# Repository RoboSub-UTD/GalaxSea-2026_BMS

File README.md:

# GalaxSea 2026 Battery Management System

The battery management system for GalaxSea 2026 Roboboat

## Documentation
[Add link to documentation folder here]

## Getting started 
Clone the project with `git clone https://github.com/RoboSub-UTD/GalaxSea-2026_BMS.git` 

## Prerequsities 
Ensure the following tools are installed: 
- make 
- cmake
- gcc-arm-none-eabi
- openocd 
- gdb-multiarch
- CubeMX (Standalone or included with STM32CubeIDE)

> [!NOTE] 
> Installation of some of these tools on a Windows environment may require use of toolchains such as MYSY2 or Cygwin. Installing Windows Subsystem for Linux (WSL2) or using a Linux virtual machine are both viable alternatives.

### Installing USB Passthrough (WSL2)
Read this section if you are setting up your build environment through WSL2. You may skip this section otherwise.

USB passthrough is required for WSL2 because WSL2 is essentially a lightweight VM that does not have access to external USB devices by default. We can allow WSL to access USB devices through the use of usbipd-win which can be installed via the following link. The link also includes instructions on how to bind usb devices to WSL2.

usbipd-win Installation Link: https://github.com/dorssel/usbipd-win

> [!TIP]
> Binding devices using usbipd-win requires using the command line. If you prefer to use a GUI then it's reccomended to install 
> `wsl-usb-manager` here 
> https://github.com/nickbeth/wsl-usb-manager

## Recommended VS Code extensions
```
twxs.cmake
marus25.cortex-debug
ms-vscode.vscode-serial-monitor
ms-vscode.makefile-tools
ms-vscode.cmake-tools
ms-vscode.cpptools
ms-vscode.cpptools-extension-pack
ms-vscode.cpptools-themes
mcu-debug.rtos-views
mcu-debug.debug-tracker-vscode
mcu-debug.memory-view
mcu-debug.peripheral-viewer
```

## How to run Firmware

`cwd = bms`  

1. mkdir build && cd build 
2. cmake .. 
3. cmake --build build
## How to Contribute: 

Development of new features will be done on a separate branch other than main and will be merged with a pull request

## ARM Cortex Debug Configuration 
ARM Cortex Debug is a handy VS Code extension that integrates a IDE-like debugger for ARM microcontrollers into VS Code. To set up the debugger follow the instructions below.

1. Type the following command in the top bar: `>Debug: Add Configuration` to generate a 
`launch.json` file in the `.vscode` directory (usually hidden by default). 

2. Navigate and open up the `.vscode/launch.json` file.

3. Copy and paste the following JSON formatted code into the `launch.json` file. This will enable the use of openocd and gdb-mulitarch
by the Cortex Debug extension.

```
{
    "version": "0.2.0",
    "configurations": [
        {
            "name": "Debug (OpenOCD)",
            "cwd": "${workspaceFolder}",
            "executable": "${workspaceFolder}/bms/build/bms.elf",
            "request": "launch",
            "type": "cortex-debug",
            "servertype": "openocd",
            "interface": "swd",
            "device": "STM32H7532ZI",
            "runToEntryPoint": "main",
            "showDevDebugOutput": "raw",
            "configFiles": [
                "/usr/share/openocd/scripts/interface/stlink.cfg",
                "/usr/share/openocd/scripts/target/stm32h7x.cfg"
            ],
            "preLaunchCommands": [
                "set mem inaccessible-by-default off",
                "monitor reset"
            ],
            "postLaunchCommands": [
                "monitor reset init",
                "monitor sleep 200"
            ],
            "armToolchainPath": "/usr/bin/",
            "gdbPath": "/usr/bin/gdb-multiarch"
        }
    ]
}
```

4. Next, build and compile the binary executable for the project if you haven't already. 

5. Now, press the `Run` option on the top toolbar and select the first option `Start Debugging`
to start a session of Cortex debug. Cortex debug should flash the program to the MCU and highlight the starting point of the program in yellow. On the top right, a toolbar should appear with a few commands for debugging the program.

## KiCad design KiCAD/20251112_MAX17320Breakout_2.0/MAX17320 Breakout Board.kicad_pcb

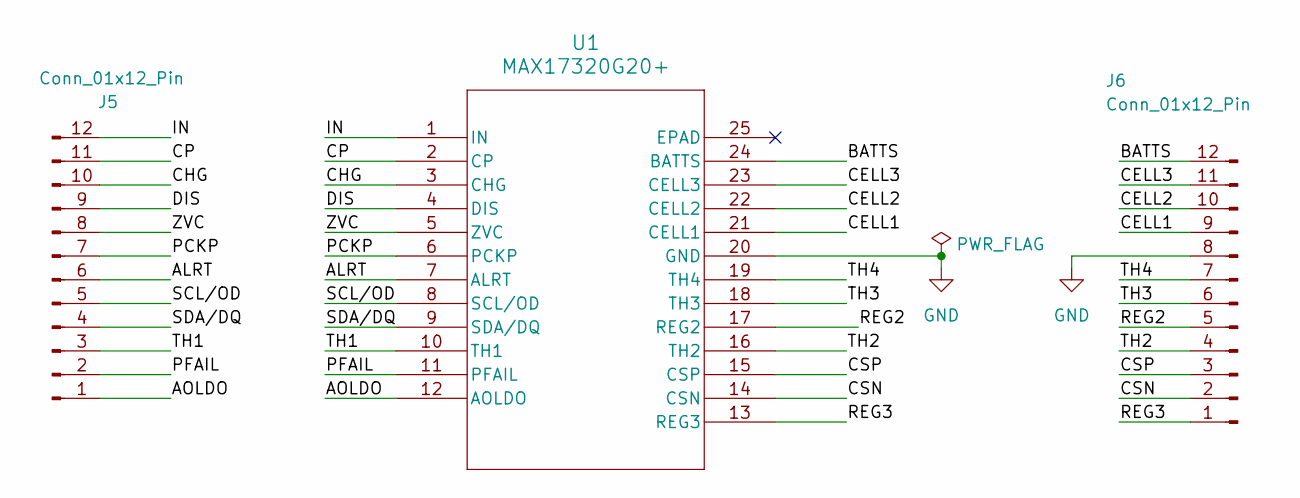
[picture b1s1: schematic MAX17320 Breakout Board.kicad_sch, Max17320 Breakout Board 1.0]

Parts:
J5, J6: Conn_01x12_Pin; PinHeader_1x12_P2.54mm_Vertical
U1: MAX17320G20+; 21-0139I_T2444-4_MXM

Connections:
/ALRT: J5.6, U1.7 (ALRT)
/AOLDO: J5.1, U1.12 (AOLDO)
/BATTS: J6.12, U1.24 (BATTS)
/CELL1: J6.9, U1.21 (CELL1)
/CELL2: J6.10, U1.22 (CELL2)
/CELL3: J6.11, U1.23 (CELL3)
/CHG: J5.10, U1.3 (CHG)
/CP: J5.11, U1.2 (CP)
/CSN: J6.2, U1.14 (CSN)
/CSP: J6.3, U1.15 (CSP)
/DIS: J5.9, U1.4 (DIS)
/IN: J5.12, U1.1 (IN)
/PCKP: J5.7, U1.6 (PCKP)
/PFAIL: J5.2, U1.11 (PFAIL)
/REG2: J6.5, U1.17 (REG2)
/REG3: J6.1, U1.13 (REG3)
/SCL/OD: J5.5, U1.8 (SCL/OD)
/SDA/DQ: J5.4, U1.9 (SDA/DQ)
/TH1: J5.3, U1.10 (TH1)
/TH2: J6.4, U1.16 (TH2)
/TH3: J6.6, U1.18 (TH3)
/TH4: J6.7, U1.19 (TH4)
/ZVC: J5.8, U1.5 (ZVC)
GND: J6.8, U1.20 (GND)

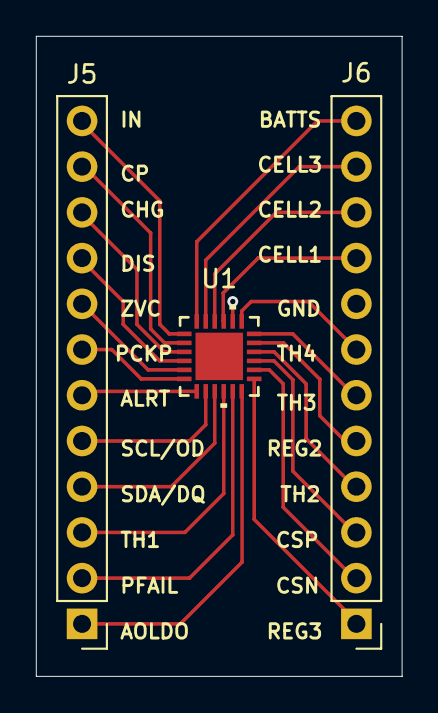
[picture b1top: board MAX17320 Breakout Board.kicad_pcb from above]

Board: 2 copper layers, 20.3 x 35.6 mm, 3 parts (0 on the bottom side), 24 nets.

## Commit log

2025-11-15 Uploaded BreakoutBoard KiCad files
2026-02-09 Initial CubeMX project generation
2026-02-09 update gitignore
2026-02-09 CMake automatically checks for gcc-arm-none-eabi.cmake file
2026-02-09 update README firmware instructions
2026-02-09 Updated README: gdb-multiarch should also be installed
2026-02-12 Instructions for ARM Cortex Debug were added
2026-02-14 Updated README with USB passthrough tutorial
